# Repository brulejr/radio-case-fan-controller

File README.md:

# Radio Case Fan Controller

ESP32 + ESPHome temperature-controlled fan module for cooling enclosed radio
equipment cases (initial target: the ICOM IC-2730A compact organizer, reusable
for other go-box modules). Supports one Noctua 5V PWM fan (outbound only,
passive intake) or two (matched outbound + inbound), switchable in software.

## Status

**Working prototype, in production use.** Built on a protoboard carrier and
running in the radio case: temperature-driven fan control, dual-fan operation
and RPM monitoring are all verified on hardware.

The custom carrier PCB (rev A) is drawn and checked — see
[`hardware/pcb/`](hardware/pcb/) — and is ready to order.
The enclosure follows. Breadboard was development-lab only and is behind us.

## Hardware on hand

- ESP32-C6-WROOM-1 dev board (RISC-V, 2×15 headers, dual USB-C)
- HiLetgo DS18B20 waterproof temperature probe (1-Wire, stainless steel, ~380 mm cable)
- Noctua NF-A4x20 5V PWM fan(s)
- 12V → 5V buck converter with a **USB-C output** (any module ≥1A)

## Schematic

[`hardware/schematic.svg`](hardware/schematic.svg) — full electrical diagram.
[`docs/wiring.md`](docs/wiring.md) has the net-by-net connection table, the
connector pinouts, the BOM, and the order to bring the board up in.

## Pinout (ESP32-C6-WROOM-1 dev board)

| Signal                | GPIO   | Side   | Notes                                            |
| --------------------- | ------ | ------ | ------------------------------------------------ |
| DS18B20 data (1-Wire) | GPIO6  | Left   | 4.7kΩ pull-up to 3.3V between data and VCC       |
| Fan 1 (outbound) PWM  | GPIO20 | Right  | Hardware LEDC output, 25kHz per Noctua PWM spec  |
| Fan 1 tach            | GPIO21 | Right  | Open-collector; 10kΩ pull-up to **3.3V**, not 5V |
| Fan 2 (inbound) PWM   | GPIO18 | Right  | Hardware LEDC output, 25kHz                      |
| Fan 2 tach            | GPIO19 | Right  | Open-collector; 10kΩ pull-up to **3.3V**, not 5V |

Pins chosen to avoid the C6 strapping pins (4, 5, 8, 9, 15 — 8 also drives the
onboard RGB LED, 9 is the BOOT button, 15 has no internal pull), the USB
Serial/JTAG pair (12, 13), and the UART0 pins wired to the USB bridge (16, 17).
GPIO14 is not broken out, and GPIO24–30 are consumed by the SPI flash bus.

The four fan signals sit as a contiguous block on the right header while the
1-Wire probe is on the left, putting it on the physically opposite side of the
board from the 25kHz PWM edges. Spare after this: GPIO0, 1, 2, 3, 7, 10, 11,
22, 23.

## Power wiring

- Radio supply (12V nominal, wide tolerance) → buck converter input, direct.
  No protection components by design — the box is fed from a battery or bench
  supply, which handle surge and reverse polarity at the source
- The buck's only output is **USB-C**, so 5V reaches the board through a USB-C
  cable into one of the dev board's two ports
- Both fans take 5V and GND from the dev board's header pins — so **fan power
  depends on the dev board**. See the power topology section of
  [`docs/wiring.md`](docs/wiring.md) for what that implies
- **One power source at a time**: the buck and both USB-C ports share a net.
  Don't leave the buck connected while a computer is plugged in
- No bulk or decoupling caps on the 5V rail; 4-pin PWM fans don't chop their
  supply current, and the dev board has its own input decoupling

## Fan PWM/tach notes

- Noctua 4-pin fans expect ~25kHz on the PWM control line; the ESP32-C6's
  hardware `LEDC` peripheral hits this natively at ~11-bit resolution (this is
  why an ESP32-class part over an ESP8266 — ESP8266's software PWM can't
  cleanly reach 25kHz and tends to produce audible whine)
- Tach line is open-collector: it only pulls low, never drives high, so a
  simple pull-up to 3.3V is safe — no level shifting needed
- Fans report 2 tach pulses per revolution; the ESPHome config's
  `pulse_counter` filter accounts for this
- **No PWM signal means full speed**, not stopped — the fan pulls its control
  input high internally. Expect a spin-up if you unplug a PWM line while the
  fan is powered
- Each fan draws 0.1A / 0.5W at full speed (Noctua spec)

## Software

`icom2370a-fan-controller.yaml` — ESPHome config. Key behavior:

- DS18B20 reading drives a linear PWM ramp between a configurable min/max
  temperature (exposed as tunable `number` entities, not hardcoded)
- "Dual Fan Mode" switch: on = both fans run the same curve; off = only
  Fan 1 (outbound) runs, Fan 2 output held at 0% for passive-intake mode
- Fallback WiFi AP + local API so the module stays controllable if the
  field WiFi network isn't up
- Local web UI at `http://<device-ip>/` for the sensors, fan-curve numbers and
  Dual Fan Mode switch, with its assets embedded in flash so it works with no
  internet. Needs `web_server_username` / `web_server_password` in `secrets.yaml`

### First flash

1. Copy `secrets.yaml.example` to `secrets.yaml` and fill in your values
2. Flash. The boot log lists the 1-Wire devices found on GPIO6; confirm the
   probe enumerates. No address needs configuring — see the note in the YAML
3. Confirm fan curve thresholds via Home Assistant or the ESPHome web UI
   before buttoning up the enclosure

## Repo layout

```
/esphome/icom2370a-fan-controller.yaml    # ESPHome config
/esphome/secrets.yaml.example
/hardware/schematic.svg                    # schematic / wiring diagram
/hardware/esp32-photo.jpg                  # dev board + protoboard carrier, for the header map
/hardware/pcb/                             # KiCad 8 carrier PCB, rev A
/docs/wiring.md                            # net list, connection table, BOM, bring-up order
README.md
.gitignore
```

Still to come under `/hardware/`: the OpenSCAD enclosure.

## Problem solving

Lessons from first bring-up on real hardware. [`docs/wiring.md`](docs/wiring.md)
carries the electrical detail.

### Start with the `[D][fan]` log line

It prints every 5s and shows the live setpoints alongside the computed duty:

```
[D][fan:197]: t=32.88 lo=25.0 hi=45.0 floor=0.30 -> duty=0.674 dual=1
```

The three setpoints are `restore_value: true`, so whatever you last set from the
web UI or Home Assistant **outranks `initial_value` in the YAML** and survives
both reboots and OTA updates. Trust this line, not the config file.

### Symptom table

| Symptom | Likely cause |
| ------- | ------------ |
| Fan runs constantly, RPM flat `0.00`, no response to duty changes | PWM and tach swapped at the fan connector. Verify by **wire colour** — blue is PWM, green is tach — because pin numbering is exactly what's unreliable when this happens |
| Fan runs at full speed | No PWM signal reaching it. An open control line is held high by the fan's internal pull-up, which reads as 100% duty |
| Fan seems to idle quietly | It may in fact be at 100%. An NF-A4x20 is only ~18 dB(A) flat out, so full speed and idling sound alike without a reference |
| Fan turns at 0% duty | Something is wrong upstream — this fan **does** stop at 0%, verified on the bench |
| RPM reads `0.00` while the fan spins | Tach pull-up on the wrong rail, or the tach line open. A spinning fan's tach reads ~1.6V on a DC meter; a flat rail voltage means no pulses |
| Low hum on nearby 2 m / 70 cm radios while the fans run | Check both tach pull-up joints (R2/R3, 10 kΩ) first — a disconnected one was found during the investigation. RC filters, ferrites and the probe made no difference. Not yet fully resolved |
| RPM reads absurdly high (~234,000) | The `multiply` filter is wrong. `pulse_counter` reports pulses/min, so RPM = pulses/min ÷ 2 |

### Techniques worth remembering

**Raw versus published values.** `[D][pulse_counter]` prints the raw
`pulses/min`, untouched by filters. Comparing it against the published RPM
separates a sensor problem from a scaling problem.

**Measure at both ends of a wire.** Continuity from a GPIO to a header pin says
nothing about whether the fan's own conductor is landed there. Assuming it did
cost several rounds of diagnosis.

**Slow RPM feedback?** The pulse counters run at `update_interval: 60s`. Drop
them to `10s` temporarily while chasing a tach problem, then put them back.

**Changing setpoints without Home Assistant.** The device serves a local page at
`http://<device-ip>/` with the fan-curve numbers and the Dual Fan Mode switch.
Assets are embedded in flash, so it works with no internet.

**RF interference tests: no temperature means no PWM.** The control loop
returns early while the temperature is invalid, so with the probe unplugged, or
with `update_interval: never`, the PWM lines never switch and the fans get no
commanded duty. Any test that removes the probe therefore also changes the fans.
To separate them, leave the probe in and move **Fan Curve Min Temp** above or
below the case temperature — and **confirm from the `[D][fan]` duty and the RPM
readings which fans are actually running** before judging a result.

**Reference figures.** At ~67% duty expect roughly 4,050 RPM (Fan 1,
outbound) and 3,900 RPM (Fan 2, inbound) — useful for judging whether a reading
is plausible. (Recorded before the fan pin assignments were corrected, when the
entity names were swapped; the figures are attributed to the physical fans.)

## TODO

- [x] Design a custom PCB for the carrier board, using the protoboard build as
      the reference (rev A, [`hardware/pcb/`](hardware/pcb/))
- [x] Confirm the dev board header row spacing (25.4 mm)
- [ ] Order the rev A boards
- [ ] Design enclosure (OpenSCAD) once the PCB is finalized
- [ ] Consider stall detection (tach == 0 while PWM > 0) as a fault alert

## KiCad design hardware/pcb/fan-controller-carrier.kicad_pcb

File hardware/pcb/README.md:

# Carrier PCB — rev A

KiCad 8 project for the custom carrier board that replaces the protoboard. The
ESP32-C6 dev board from the prototype plugs in unchanged. The buck converter
moves onto the board, so there's no USB-C cable between them. Every passive is
**through-hole**, for hand assembly.

| File                                 | What                                      |
| ------------------------------------ | ----------------------------------------- |
| `fan-controller-carrier.kicad_sch`   | schematic                                 |
| `fan-controller-carrier.kicad_pcb`   | layout, 2-layer, 1.6 mm                   |
| `carrier-top.svg`                    | preview render (copper + silk)            |
| `fit-template.pdf`                   | 1:1 printable outline for space checking  |

Only stock KiCad 8 libraries are used. Nothing needs installing beyond KiCad.
ERC, DRC and schematic parity are all clean.

## Dev board header spacing

The socket rows J5/J6 are **25.4 mm (10 × 0.1") apart, centre to centre**,
confirmed against the dev boards on hand (2026-10-01). Boards of this type come
in 0.1" steps (22.86 / 25.4 / 27.94 mm), so a different dev board needs
checking before reuse. To change it, move J6 and re-route the filter block
between the rows.

## Board

- **90 × 54 mm**, sized for a **Hammond 1590B** die-cast box (inside 107 ×
  55.4 mm at the floor, 27 mm deep). The board sits between the lid-screw
  bosses with about 0.7 mm spare on each long side.
- 4 × M3 holes, 3.5 mm in from each corner. They are **not plated**, and there
  is a 3.6 mm copper keepout around each one. The screw heads and standoffs
  never touch GND, so board ground stays isolated from the enclosure.
- The bottom layer is almost entirely GND. It carries only the 5 V feed to the
  fans and two short tach links in the filter block.

### Height stack

| Item                                         | mm, approx. |
| -------------------------------------------- | ----------- |
| standoff                                     | 5           |
| carrier PCB                                  | 1.6         |
| female socket                                | 8.5         |
| dev board + USB-C / module                   | 5           |
| **top of dev board above enclosure floor**   | **~20**     |

U1, the electrolytics (~10–11 mm) and the fan plugs (~12 mm above the PCB) are
lower than that, which leaves about 7 mm under the 1590B's lid.

The filter block and R1 sit **under the dev board**, inside the 8.5 mm socket
gap. Lay the resistors flat and seat the disc capacitors low, with no more
than ~6 mm of body and leads above the board.

## Layout

```
 x=0 (left end panel)                                        x=90 (right end panel)
 ┌──────────────────────────────────────────────────────────────────┐
 │ H1                                                           H2  │
 │ J4 probe (XH, top) R6 C7 ─ top edge ─▶ GPIO6   ┌── dev board ──┐│
 │                                                │ J5 RST ... 5V ││ ANTENNA
 │ J1 12V  U1 R-78E      12V/USB warning   ◀USB  │  filter block ││ keepout
 │         C1 C2                                  │ J6 GND ... 5V ││
 │ J3 FAN2  J2 FAN1  C9 C8  5V FANS ONLY ◀─ lanes ─└───────────────┘│
 │ H3                                                           H4  │
 └──────────────────────────────────────────────────────────────────┘
```

- **Left end:** J1 (12 V) has its wire entry facing the left edge. J4 (probe)
  takes its plug from above. Both fan headers are in the bottom-left corner,
  also plugged from above, so the board can lie flat facing up.
- **Dev board:** the USB end points into the board and the antenna end
  overhangs the right edge, with a copper keepout under the antenna on both
  layers.
- **Filter block,** between the socket rows, in four rows starting nearest J6:

  | Row | Parts | Channel |
  | --- | ----- | ------- |
  | A | R4 + C3 | PWM1, GPIO20 |
  | B | R5 + C4 | PWM2, GPIO18 |
  | C | C5 + R2 | TACH1, GPIO21 |
  | D | C6 + R3 | TACH2, GPIO19 |

  Each filtered PWM line passes between two adjacent socket pins (0.3 mm track,
  0.27 mm clearance) to reach its lane. The tach parts connect on the bottom
  layer, so the tach and PWM lines never cross.
- **Fan lanes:** four non-crossing traces run to the headers, 1.5 mm apart:
  - GPIO18/19 → J3 (Fan 2, inbound, left header)
  - GPIO20/21 → J2 (Fan 1, outbound, right header)
- **1-Wire:** runs along the top edge, on the opposite side of the board from
  the fan lanes.

## Filtering

Rationale for each filter, from the prototype's RF interference investigation:

| Parts | Where | Why |
| ----- | ----- | --- |
| **C5/C6** 1 nF, with R2/R3 10 kΩ | tach lines, at the GPIO | The one prototype change that clearly reduced the hum was restoring a lost 10 kΩ tach pull-up. The likely mechanism is PWM edges coupling onto a weakly held tach line. The cap shunts that coupling; the 10 µs time constant is far shorter than the ≥ 6 ms between tach pulses. |
| **R4/C3, R5/C4** 220 Ω + 10 nF | PWM lines, at the GPIO | Insurance. It made no difference to the hum on the prototype, but it's proven harmless (fan control works through it) and it softens edges that run beside the tach wire in each fan cable. |
| **R6** 0 Ω, **C7** not fitted | 1-Wire, at J4 | Spare footprints: a ferrite and an RC on this line made no difference on the prototype. If C7 is ever fitted, keep it **≤ 470 pF**, or the 1-Wire bus stops working. |
| **C8/C9** 10 µF + 100 nF | fan 5 V, beside J2 | Standard decoupling, shared by both headers. |

The interference wasn't fully resolved on the prototype. See **RF interference**
below.

## Connectors

| Ref | Part | Mates with |
| --- | ---- | ---------- |
| J1 | 2-pos screw terminal, 5.08 mm (Phoenix MKDS 1,5/2-5,08) | 12 V leads, or a Powerpole pigtail |
| J2, J3 | 4-pin PC fan header, Molex 47053-1000 (DigiKey WM4330-ND) | the fan's own connector, via a 4-pin PWM extension such as the Noctua NA-EC1 (30 cm; chainable) |
| J4 | JST XH 3-pin, top entry (**B3B-XH-A**) — the plug goes straight down | XHP-3 housing + SXH crimps on the probe leads, or a pre-crimped XH pigtail soldered and heat-shrunk to them |

- **XH pitch is 2.50 mm,** not 2.54 mm, even though it's often sold as 2.54.
- **Meter the probe's wires before crimping.** Some batches use white for data.
- **The XH latch is friction only.** In the go-box, add a dab of RTV silicone
  or a cable tie.
- **Keep the fan extensions keyed and 4-wire.** A PWM/tach swap has bitten this
  build before, and some cheap extensions are 3-wire and drop PWM.

## Changes from the protoboard build

| | Protoboard | PCB rev A |
| -- | -- | -- |
| Buck | USB-C-output module, off-board, cable into dev board | **R-78E5.0-1.0** SIP-3 switching regulator on board (U1), with C1 10 µF / C2 22 µF |
| 5 V to dev board | USB-C cable | U1 drives the socket's two **5V pins** (= dev board VBUS) |
| Fan 5 V | from the dev board's 5V pins | straight from U1. Fans no longer depend on the dev board |
| Fans | screw terminals | keyed 4-pin headers + extension cables |
| Probe | screw terminal | JST XH |
| Filtering | none | see **Filtering** above |
| Everything else | — | same nets, GPIOs and pull-up values |

The "one power source at a time" rule still applies, and it is printed on the
silkscreen. With 12 V on the board, the dev board's USB VBUS is live. **Unplug
12 V before plugging in a USB cable.** Flash over OTA once the board is in the
box.

Input protection is still deliberately absent. See
[`docs/wiring.md`](../../docs/wiring.md).

## BOM

| Ref      | Part                                                   | Footprint                          |
| -------- | ------------------------------------------------------ | ---------------------------------- |
| U1       | RECOM R-78E5.0-1.0 (or Murata OKI-78SR-5/1.5, same pinout) | SIP-3, 2.54 mm                 |
| C1       | 10 µF 25 V electrolytic                                | radial, 5 mm dia, 2.0 mm lead pitch |
| C2       | 22 µF 16 V electrolytic                                | radial, 5 mm dia, 2.0 mm lead pitch |
| C8       | 10 µF 16 V electrolytic                                | radial, 5 mm dia, 2.0 mm lead pitch |
| C3, C4   | 10 nF ceramic (code 103)                               | disc/MLCC, 2.5 mm lead pitch        |
| C5, C6   | 1 nF ceramic (code 102)                                | disc/MLCC, 2.5 mm lead pitch        |
| C9       | 100 nF ceramic (code 104)                              | disc/MLCC, 2.5 mm lead pitch        |
| C7       | **not fitted** (≤ 470 pF if ever used)                 | disc/MLCC, 2.5 mm lead pitch        |
| R1       | 4.7 kΩ, ¼ W                                            | axial, 7.62 mm pitch               |
| R2, R3   | 10 kΩ, ¼ W                                             | axial, 7.62 mm pitch               |
| R4, R5   | 220 Ω, ¼ W                                             | axial, 7.62 mm pitch               |
| R6       | 0 Ω jumper (or a wire link)                            | axial, 7.62 mm pitch               |
| J1       | 2-pos screw terminal, 5.08 mm                          | THT                                |
| J2, J3   | 4-pin PC fan header, Molex 47053-1000                  | THT                                |
| J4       | JST B3B-XH-A (top entry)                               | THT                                |
| J5, J6   | 1 × 15 female header, 2.54 mm, 8.5 mm tall             | THT                                |
| H1–H4    | M3 standoffs, nylon or metal (holes are isolated)      | —                                  |

Electrolytic polarity: the square pad is **+**.

## RF interference — under investigation

The protoboard puts a low hum on nearby 2 m / 70 cm radios while Fan 1 is
running. A **disconnected 10 kΩ tach pull-up** on the outbound fan (GPIO21) was
found and resoldered, and the hum stopped on the bench, but it returned once
the unit was reassembled in place. The pull-up is at least a contributor; the
full cause is not yet confirmed.

Ruled out along the way:
- the buck converter
- the fan motors
- the probe and 1-Wire line (a ferrite and an RC filter on it made no difference)
- PWM edge speed (220 Ω + 10 nF on either PWM line made no difference)

Likely mechanism: with only the ESP32's ~45 kΩ internal pull-up, PWM edges couple
onto the tach line and nudge it through the logic threshold. The software pulse
counter takes an interrupt on every glitch. Its 13 µs filter discards them, so
RPM still reads plausibly while the CPU is being woken constantly.

This board's tach capacitors target that mechanism. Whatever the full answer,
**R2 and R3 are not optional.**

## Wi-Fi in an aluminum box

The dev board's PCB trace antenna is at the right-hand end of the board, and a
closed aluminum enclosure largely blocks it. Cooling does not need the network
(`reboot_timeout: 0s`), but the web UI, Home Assistant and OTA do. If you need
them, give the right end panel a plastic insert or a window in front of the
antenna.

## Fit template

`fit-template.pdf` is the board at 1:1 on an A4 landscape page. It shows the
outline, the part outlines, the dev board's footprint and crosshairs at the
M3 holes, with approximate part heights in a legend.

Print it at **100% / Actual size**, not "Fit to page". The page also fits US
Letter. Then check the 50 mm scale bar with a ruler before trusting the
outline.

## Fabrication outputs

These are not committed (`hardware/pcb/fab/` is git-ignored). Regenerate them
from this directory with:

```
mkdir -p fab/out
kicad-cli pcb export gerbers --layers F.Cu,B.Cu,F.SilkS,B.SilkS,F.Mask,B.Mask,Edge.Cuts \
    --subtract-soldermask -o fab/out/ fan-controller-carrier.kicad_pcb
kicad-cli pcb export drill --format excellon --excellon-units mm \
    --excellon-zeros-format decimal --excellon-separate-th \
    --generate-map --map-format gerberx2 -o fab/out/ fan-controller-carrier.kicad_pcb
cd fab/out && zip ../fan-controller-carrier-revA-gerbers.zip \
    *.gtl *.gbl *.gto *.gbo *.gts *.gbs *.gm1 *-PTH.drl *-NPTH.drl
```

Upload the zip as-is to JLCPCB, PCBWay or OSH Park. The drill maps
(`*-drl_map.gbr`) stay out of the zip; they're for people, and some fabs' file
detection trips over them.

Expected contents, useful for checking a fab's preview:

| | |
| --- | --- |
| Outline | 90.00 × 54.00 mm |
| Plated holes | 93: 17 vias 0.3 mm, 30 × 0.8, 3 × 0.95 (J4), 33 × 1.0, 8 × 1.02 (fan headers), 2 × 1.3 (J1) |
| Non-plated holes | 6: 4 × 3.2 mm (M3), 2 × 1.1 mm (fan-header pegs) |

Order settings: 2 layers, 1.6 mm, 1 oz copper, any soldermask colour, HASL
(lead-free) or ENIG. The narrowest trace and gap (0.3 / 0.27 mm) and the
smallest via (0.3 mm drill) are within every fab's standard limits.

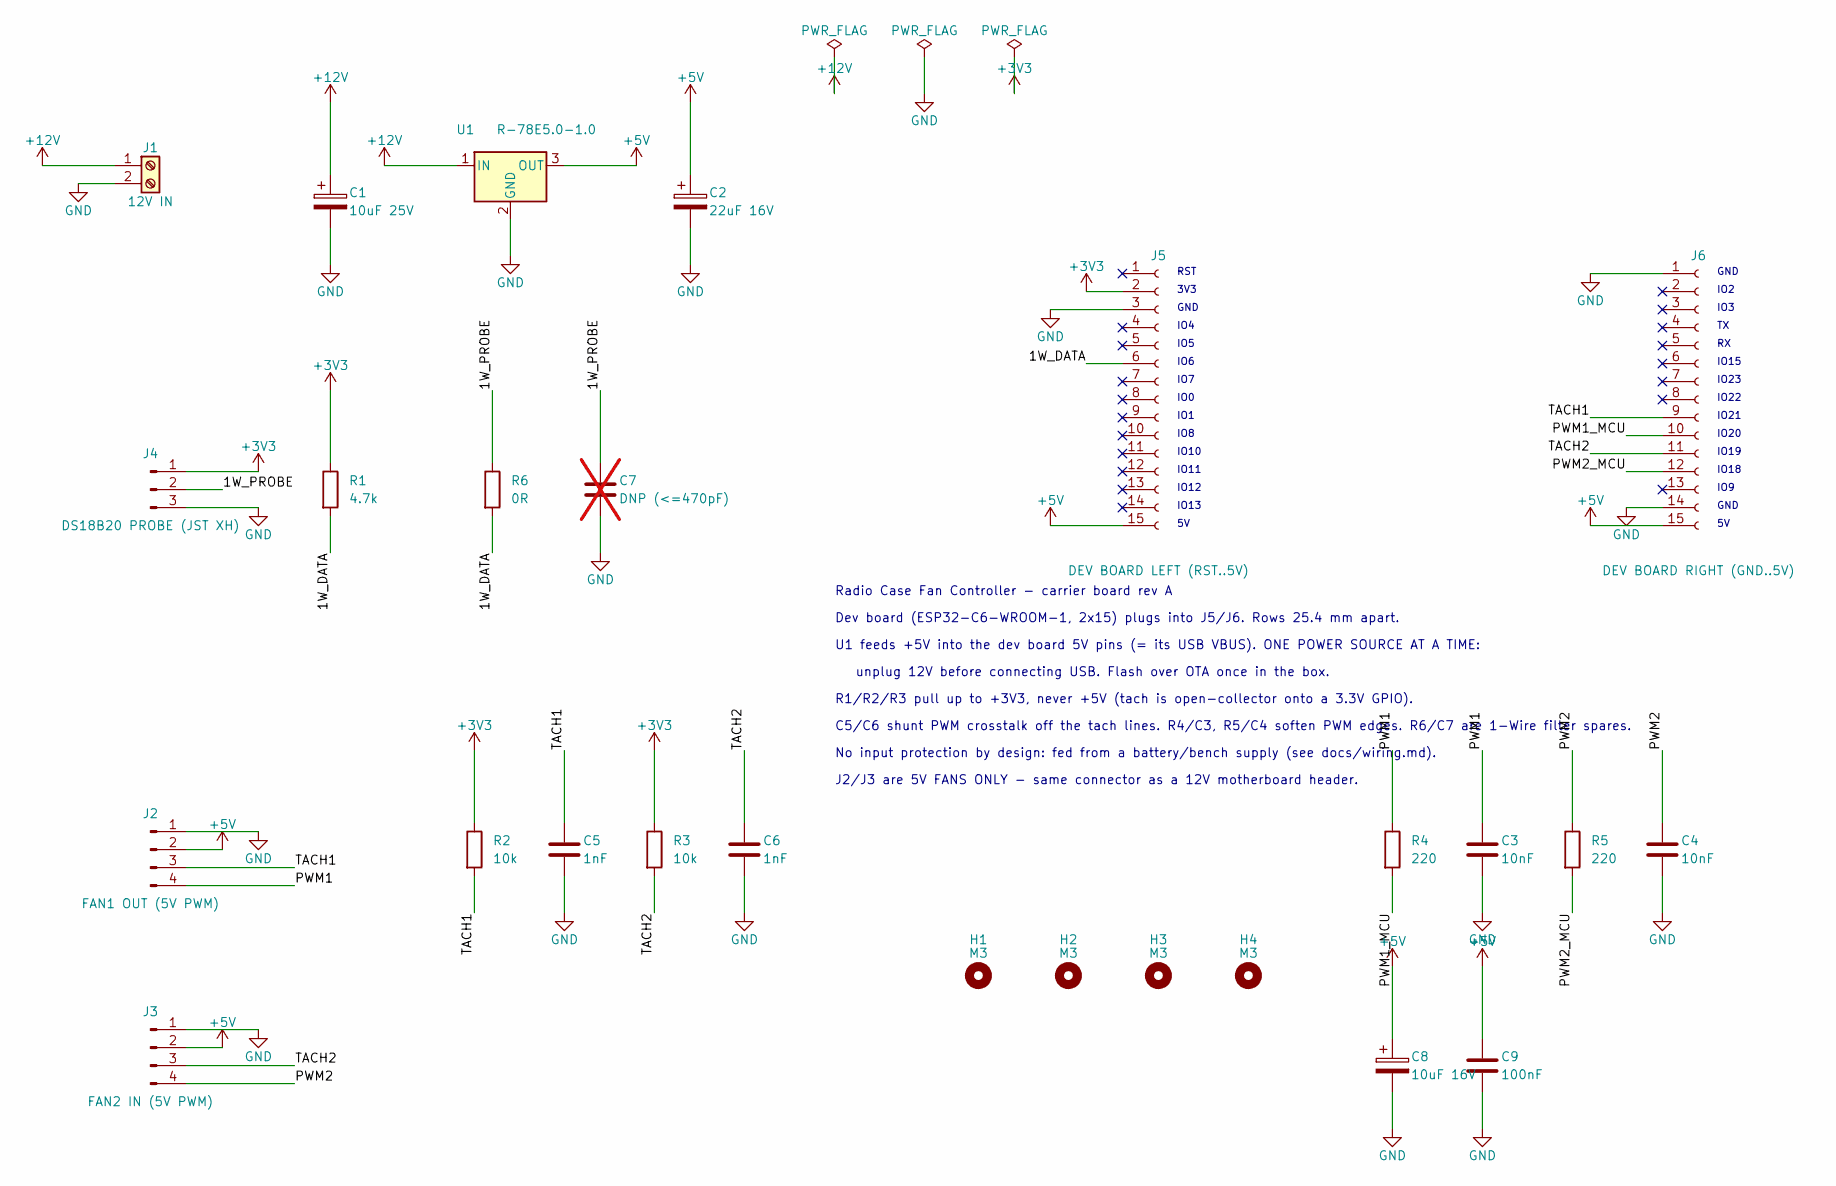
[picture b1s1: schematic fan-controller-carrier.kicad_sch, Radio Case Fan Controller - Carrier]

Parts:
C1: 10uF 25V; CP_Radial_D5.0mm_P2.00mm
C2: 22uF 16V; CP_Radial_D5.0mm_P2.00mm
C3, C4: 10nF; C_Disc_D3.8mm_W2.6mm_P2.50mm
C5, C6: 1nF; C_Disc_D3.8mm_W2.6mm_P2.50mm
C7: DNP (<=470pF); C_Disc_D3.8mm_W2.6mm_P2.50mm; not fitted
C8: 10uF 16V; CP_Radial_D5.0mm_P2.00mm
C9: 100nF; C_Disc_D3.8mm_W2.6mm_P2.50mm
H1, H2, H3, H4: M3; MountingHole_3.2mm_M3
J1: 12V IN; TerminalBlock_Phoenix_MKDS-1,5-2-5.08_1x02_P5.08mm_Horizont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
J2: FAN1 OUT (5V PWM); FanPinHeader_1x04_P2.54mm_Vertical
J3: FAN2 IN (5V PWM); FanPinHeader_1x04_P2.54mm_Vertical
J4: DS18B20 PROBE (JST XH); JST_XH_B3B-XH-A_1x03_P2.50mm_Vertical
J5: DEV BOARD LEFT (RST..5V); PinSocket_1x15_P2.54mm_Vertical
J6: DEV BOARD RIGHT (GND..5V); PinSocket_1x15_P2.54mm_Vertical
R1: 4.7k; R_Axial_DIN0207_L6.3mm_D2.5mm_P7.62mm_Horizontal
R2, R3: 10k; R_Axial_DIN0207_L6.3mm_D2.5mm_P7.62mm_Horizontal
R4, R5: 220; R_Axial_DIN0207_L6.3mm_D2.5mm_P7.62mm_Horizontal
R6: 0R; R_Axial_DIN0207_L6.3mm_D2.5mm_P7.62mm_Horizontal
U1: R-78E5.0-1.0; Converter_DCDC_RECOM_R-78E-0.5_THT

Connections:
+3V3: J4.1, J5.2, R1.1, R2.1, R3.1
+5V: C2.1, C8.1, C9.1, J2.2, J3.2, J5.15, J6.15, U1.3 (OUT)
+12V: C1.1, J1.1, U1.1 (IN)
/1W_DATA: J5.6, R1.2, R6.2
/1W_PROBE: C7.1, J4.2, R6.1
/PWM1: C3.1, J2.4, R4.1
/PWM1_MCU: J6.10, R4.2
/PWM2: C4.1, J3.4, R5.1
/PWM2_MCU: J6.12, R5.2
/TACH1: C5.1, J2.3, J6.9, R2.2
/TACH2: C6.1, J3.3, J6.11, R3.2
GND: C1.2, C2.2, C3.2, C4.2, C5.2, C6.2, C7.2, C8.2, C9.2, J1.2, J2.1, J3.1, J4.3, J5.3, J6.1, J6.14, U1.2 (GND)

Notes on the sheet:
RST
IO8
IO10
IO11
IO12
IO13
3V3
GND
IO4
IO5
IO6
IO7
IO0
IO1
IO20
IO19
IO18
IO9
IO2
IO3
IO15
IO23
IO22
IO21
Radio Case Fan Controller - carrier board rev A
Dev board (ESP32-C6-WROOM-1, 2x15) plugs into J5/J6. Rows 25.4 mm apart.
U1 feeds +5V into the dev board 5V pins (= its USB VBUS). ONE POWER SOURCE AT A TIME:
unplug 12V before connecting USB. Flash over OTA once in the box.
R1/R2/R3 pull up to +3V3, never +5V (tach is open-collector onto a 3.3V GPIO).
C5/C6 shunt PWM crosstalk off the tach lines. R4/C3, R5/C4 soften PWM edges. R6/C7 are 1-Wire filter spares.
No input protection by design: fed from a battery/bench supply (see docs/wiring.md).
J2/J3 are 5V FANS ONLY - same connector as a 12V motherboard header.

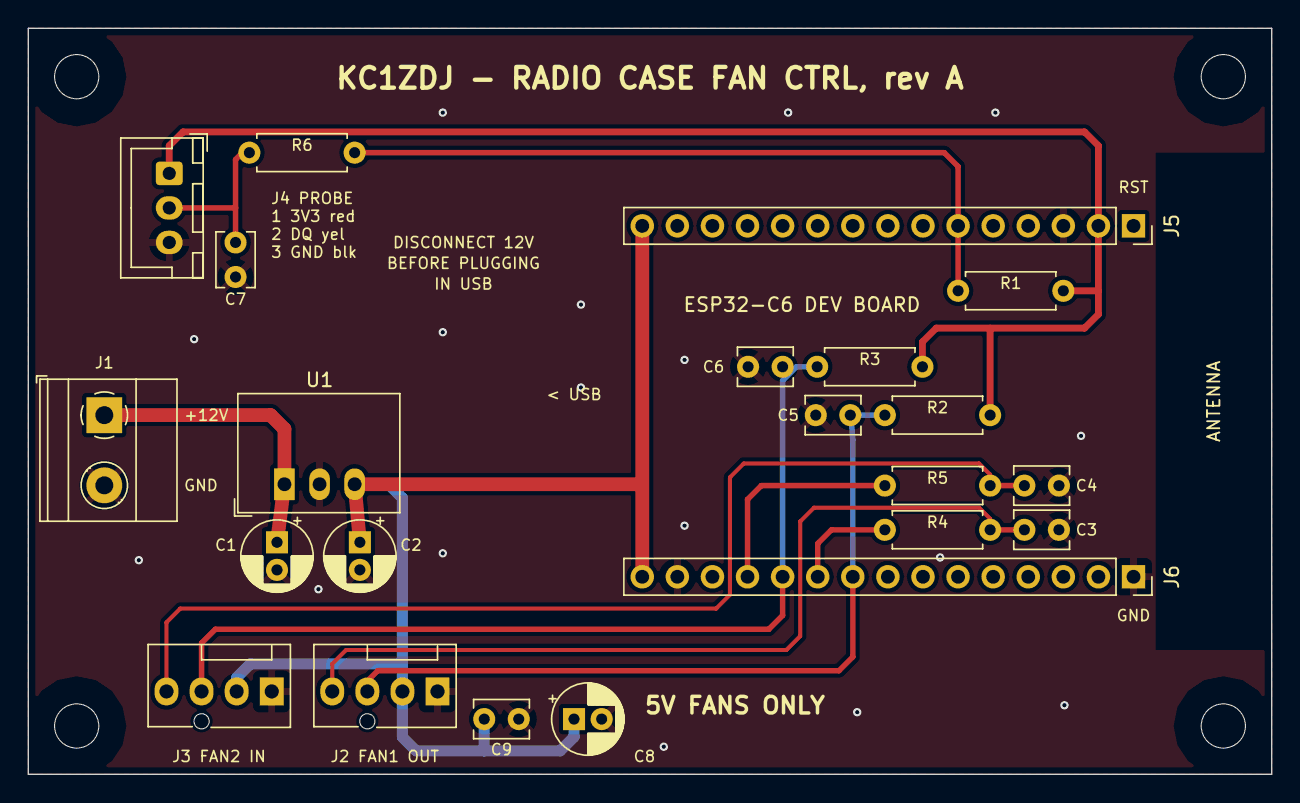
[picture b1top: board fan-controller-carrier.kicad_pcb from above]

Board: 2 copper layers, 90.0 x 54.0 mm, 26 parts (0 on the bottom side), 12 nets.
